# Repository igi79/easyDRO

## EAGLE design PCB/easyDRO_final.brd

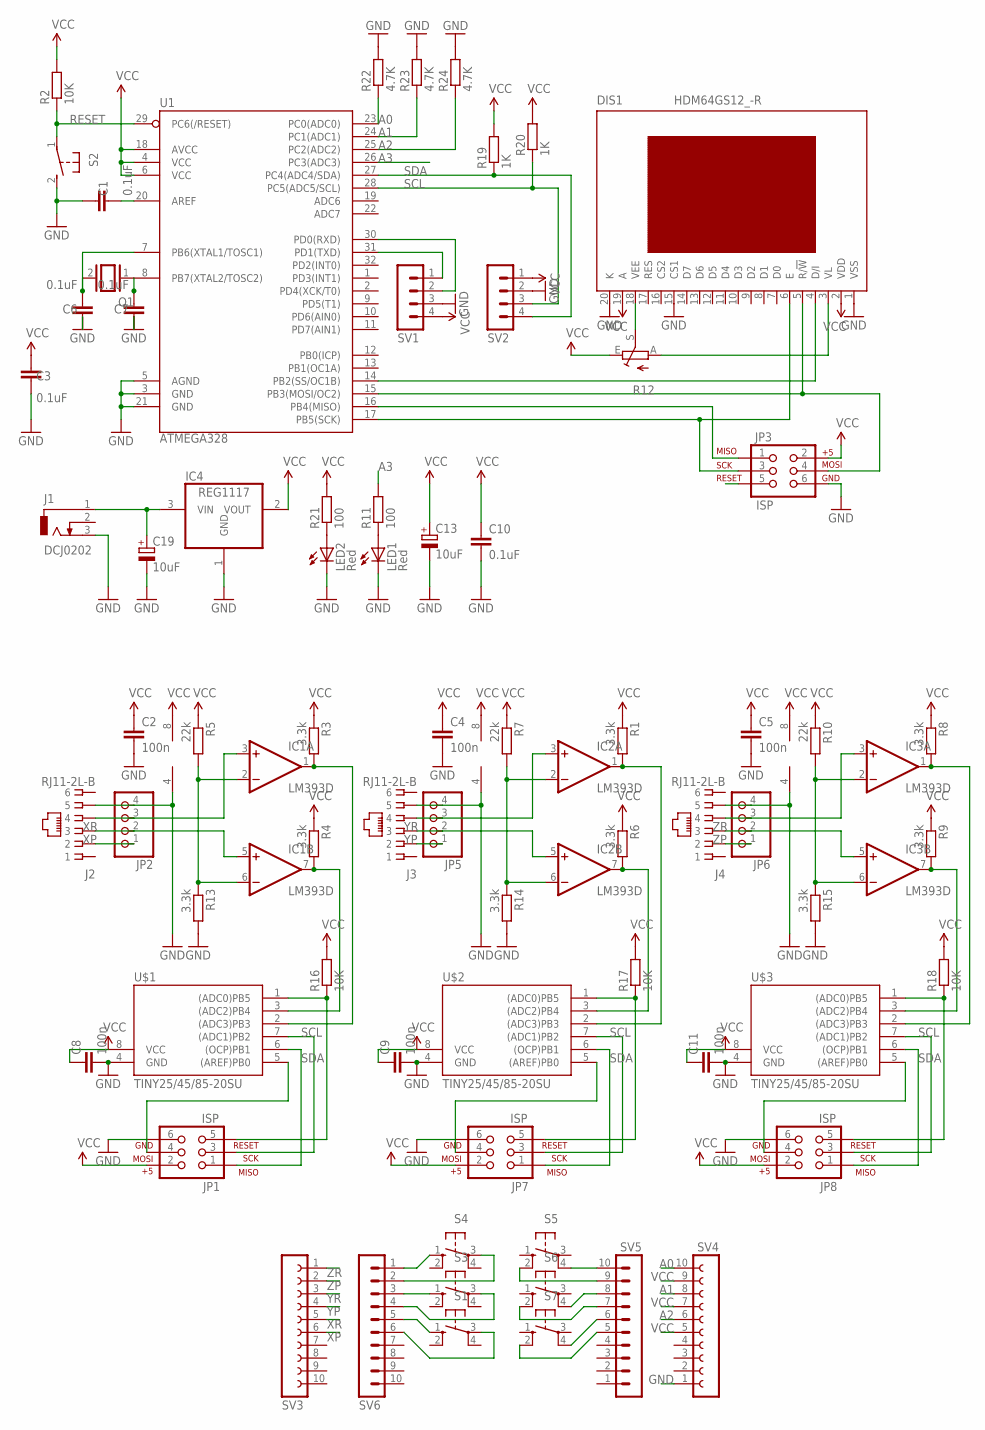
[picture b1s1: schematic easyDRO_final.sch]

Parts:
C1, C3, C6, C7, C10: 0.1uF; C0805
C2, C4, C5, C8, C9, C11: 100n; C0805
C13, C19: 10uF; E2,5-5
DIS1: HDM64GS12_-R
IC1, IC2, IC3: LM393D; SO08
IC4: REG1117; SOT223
J1: DCJ0202
J2, J3, J4: RJ11-2L-B; RJ11-NO_SHIELD
JP1, JP3, JP7, JP8: ISP; 2X3
JP2, JP5, JP6: PINHD-1X4/90; 1X04/90
LED1, LED2: Red; LED5MM
Q1: XTAL/S; QS
R1, R3, R4, R6, R8, R9, R13, R14, R15: 3.3k; R0805
R2, R16, R17, R18: 10K; R0805
R5, R7, R10: 22k; R0805
R11, R21: 100; R0805
R12: TRIM_EU-CA6H; CA6H
R19, R20: 1K; R0805
R22, R23, R24: 4.7K; R0805
S1, S3, S4, S5, S6, S7: 40-XX; B3F-40XX
S2: 31-XX; B3F-31XX
SV1, SV2: MA04-1
SV3, SV4: FE10-1; FE10
SV5, SV6: MA10-1
U1: ATMEGA328; TQFP32-08
U$1, U$2, U$3: TINY25/45/85-20SU; SOIC8

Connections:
A0: R22.1, SV4.10, U1.23 (PC0(ADC0))
A1: R23.1, SV4.8, U1.24 (PC1(ADC1))
A2: R24.1, SV4.6, U1.25 (PC2(ADC2))
A3: R11.2, U1.26 (PC3(ADC3))
CLK1: IC1.7 (OUT), R4.2, U$1.3 ((ADC2)PB4)
CLK2: IC2.7 (OUT), R6.2, U$2.3 ((ADC2)PB4)
CLK3: IC3.7 (OUT), R9.2, U$3.3 ((ADC2)PB4)
DATA1: IC1.1 (OUT), R3.2, U$1.2 ((ADC3)PB3)
DATA2: IC2.1 (OUT), R1.2, U$2.2 ((ADC3)PB3)
DATA3: IC3.1 (OUT), R8.2, U$3.2 ((ADC3)PB3)
GND: C1.2, C2.2, C3.1, C4.2, C5.2, C6.2, C7.2, C8.2, C9.2, C10.2, C11.2, C13.-, C19.-, DIS1.1 (VSS), DIS1.15 (CS1), DIS1.20 (K), IC1.4 (V-), IC2.4 (V-), IC3.4 (V-), IC4.1 (GND), J1.3, J2.5, J3.5, J4.5, JP1.6, JP2.4, JP3.6, JP5.4, JP6.4, JP7.6, JP8.6, LED1.K (C), LED2.K (C), R13.2, R14.2, R15.2, R22.2, R23.2, R24.2, S2.2 (S), SV1.3, SV2.2, SV4.1, U1.3 (GND), U1.5 (AGND), U1.21 (GND), U$1.4 (GND), U$2.4 (GND), U$3.4 (GND)
unnamed: IC1.2 (-IN), IC1.6 (-IN), R5.2, R13.1
unnamed: DIS1.6 (E), JP3.3, U1.17 (PB5(SCK))
unnamed: DIS1.5 (R/!W), JP3.4, U1.15 (PB3(MOSI/OC2))
unnamed: DIS1.4 (D/I), U1.14 (PB2(SS/OC1B))
unnamed: C7.1, Q1.1, U1.8 (PB7(XTAL2/TOSC2))
unnamed: C1.1, U1.20 (AREF)
unnamed: C6.1, Q1.2, U1.7 (PB6(XTAL1/TOSC1))
unnamed: JP1.1, U$1.6 ((OCP)PB1)
unnamed: JP1.5, R16.1, U$1.1 ((ADC0)PB5)
unnamed: JP7.1, U$2.6 ((OCP)PB1)
unnamed: JP7.5, R17.1, U$2.1 ((ADC0)PB5)
unnamed: JP8.1, U$3.6 ((OCP)PB1)
unnamed: JP8.5, R18.1, U$3.1 ((ADC0)PB5)
unnamed: SV1.1, U1.31 (PD1(TXD))
unnamed: JP3.1, U1.16 (PB4(MISO))
unnamed: DIS1.18 (VEE), R12.S
unnamed: DIS1.3 (VL), R12.A
unnamed: S5.4 (P1), SV5.10
unnamed: IC1.3 (+IN), J2.4, JP2.3
unnamed: IC2.2 (-IN), IC2.6 (-IN), R7.2, R14.1
unnamed: S5.2 (S1), SV5.9
unnamed: SV1.2, U1.30 (PD0(RXD))
unnamed: LED2.A, R21.1
unnamed: S6.4 (P1), SV5.8
unnamed: IC2.3 (+IN), J3.4, JP5.3
unnamed: S6.2 (S1), SV5.7
unnamed: IC3.2 (-IN), IC3.6 (-IN), R10.2, R15.1
unnamed: S7.4 (P1), SV5.6
unnamed: S7.2 (S1), SV5.5
unnamed: S4.1 (S), SV6.1
unnamed: IC3.3 (+IN), J4.4, JP6.3
unnamed: S4.3, SV6.2
unnamed: S3.1 (S), SV6.3
unnamed: S3.3, SV6.4
unnamed: S1.1 (S), SV6.5
unnamed: S1.3, SV6.6
unnamed: LED1.A, R11.1
RESET: JP3.5, R2.1, S2.1, U1.29 (PC6(/RESET))
SCL: JP1.3, JP7.3, JP8.3, R20.1, SV2.3, U1.28 (PC5(ADC5/SCL)), U$1.7 ((ADC1)PB2), U$2.7 ((ADC1)PB2), U$3.7 ((ADC1)PB2)
SDA: JP1.4, JP7.4, JP8.4, R19.1, SV2.4, U1.27 (PC4(ADC4/SDA)), U$1.5 ((AREF)PB0), U$2.5 ((AREF)PB0), U$3.5 ((AREF)PB0)
VCC: C2.1, C3.2, C4.1, C5.1, C8.1, C9.1, C10.1, C11.1, C13.+, DIS1.2 (VDD), DIS1.19 (A), IC1.8 (V+), IC2.8 (V+), IC3.8 (V+), IC4.2 (VOUT), JP1.2, JP3.2, JP7.2, JP8.2, R1.1, R2.2, R3.1, R4.1, R5.1, R6.1, R7.1, R8.1, R9.1, R10.1, R12.E, R16.2, R17.2, R18.2, R19.2, R20.2, R21.2, SV1.4, SV2.1, SV4.5, SV4.7, SV4.9, U1.4 (VCC), U1.6 (VCC), U1.18 (AVCC), U$1.8 (VCC), U$2.8 (VCC), U$3.8 (VCC)
VIN: C19.+, IC4.3 (VIN), J1.1
XP: J2.2, JP2.1, SV3.6
XR: IC1.5 (+IN), J2.3, JP2.2, SV3.5
YP: J3.2, JP5.1, SV3.4
YR: IC2.5 (+IN), J3.3, JP5.2, SV3.3
ZP: J4.2, JP6.1, SV3.2
ZR: IC3.5 (+IN), J4.3, JP6.2, SV3.1

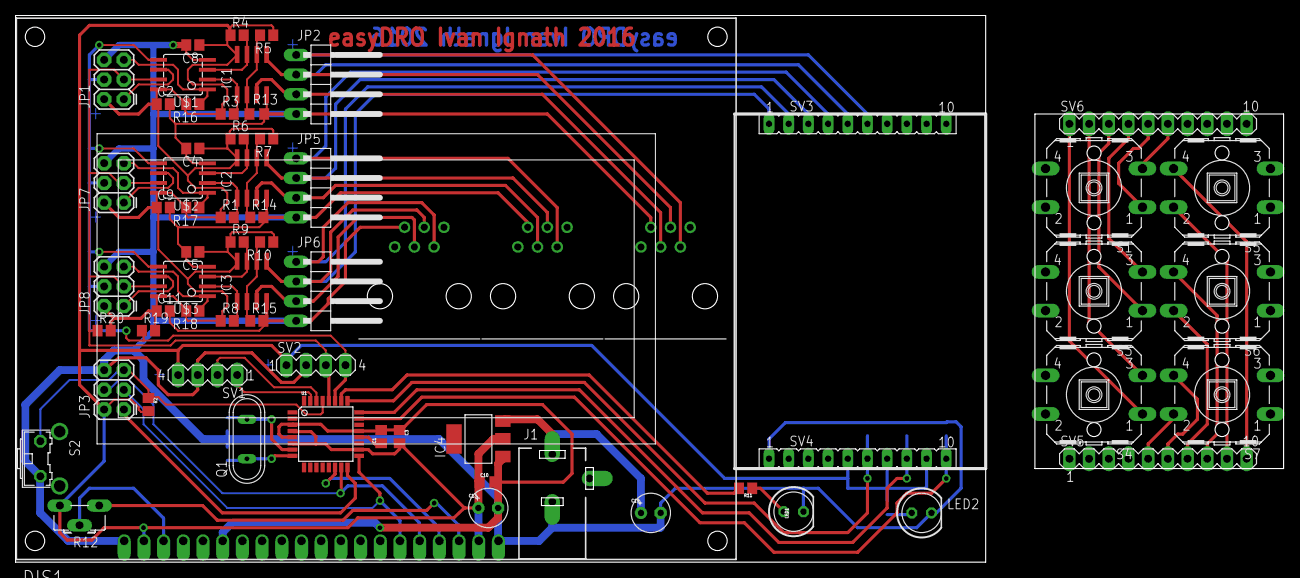
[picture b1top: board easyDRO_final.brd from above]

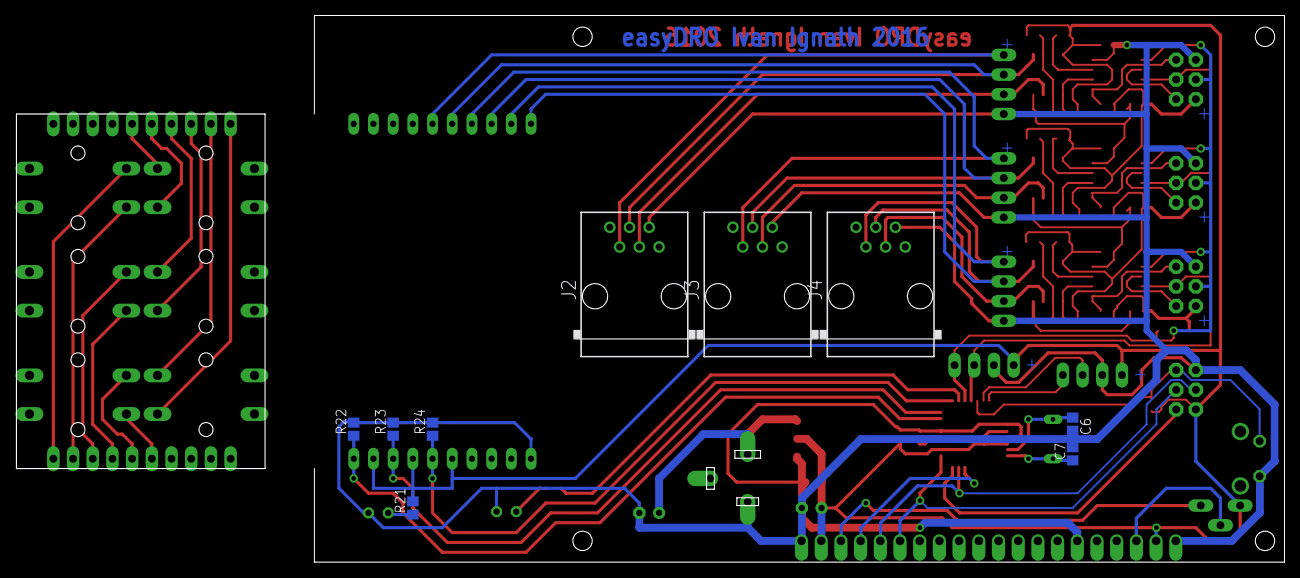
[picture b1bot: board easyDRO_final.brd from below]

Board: 2 copper layers, 163.5 x 70.5 mm, 73 parts (9 on the bottom side), 59 nets.

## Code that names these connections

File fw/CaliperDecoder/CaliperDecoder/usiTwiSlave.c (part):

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#  define DDR_USI             DDRB
#  define PORT_USI            PORTB
#  define PIN_USI             PINB
#  define PORT_USI_SDA        PB5
#  define PORT_USI_SCL        PB7
#  define PIN_USI_SDA         PINB5
#  define PIN_USI_SCL         PINB7
#  define USI_START_COND_INT  USISIF
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#  define DDR_USI             DDRB
#  define PORT_USI            PORTB
#  define PIN_USI             PINB
#  define PORT_USI_SDA        PB0
#  define PORT_USI_SCL        PB2
#  define PIN_USI_SDA         PINB0
#  define PIN_USI_SCL         PINB2
#  define USI_START_COND_INT  USISIF
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#  define DDR_USI             DDRB
#  define PORT_USI            PORTB
#  define PIN_USI             PINB
#  define PORT_USI_SDA        PB0
#  define PORT_USI_SCL        PB2
#  define PIN_USI_SDA         PINB0
#  define PIN_USI_SCL         PINB2
#  define USI_START_COND_INT  USISIF
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#  define DDR_USI             DDRB
#  define PORT_USI            PORTB
#  define PIN_USI             PINB
#  define PORT_USI_SDA        PB0
#  define PORT_USI_SCL        PB2
#  define PIN_USI_SDA         PINB0
#  define PIN_USI_SCL         PINB2
#  define USI_START_COND_INT  USISIF
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
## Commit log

2016-03-12 Final
2016-03-20 PSB in PDF
2016-03-21 Firmware
2016-04-07 Correct fw

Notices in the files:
fw/CaliperDecoder/CaliperDecoder/usiTwiSlave.c:
This program is free software; you can redistribute it and/or modify it under the
terms of the GNU General Public License as published by the Free Software
